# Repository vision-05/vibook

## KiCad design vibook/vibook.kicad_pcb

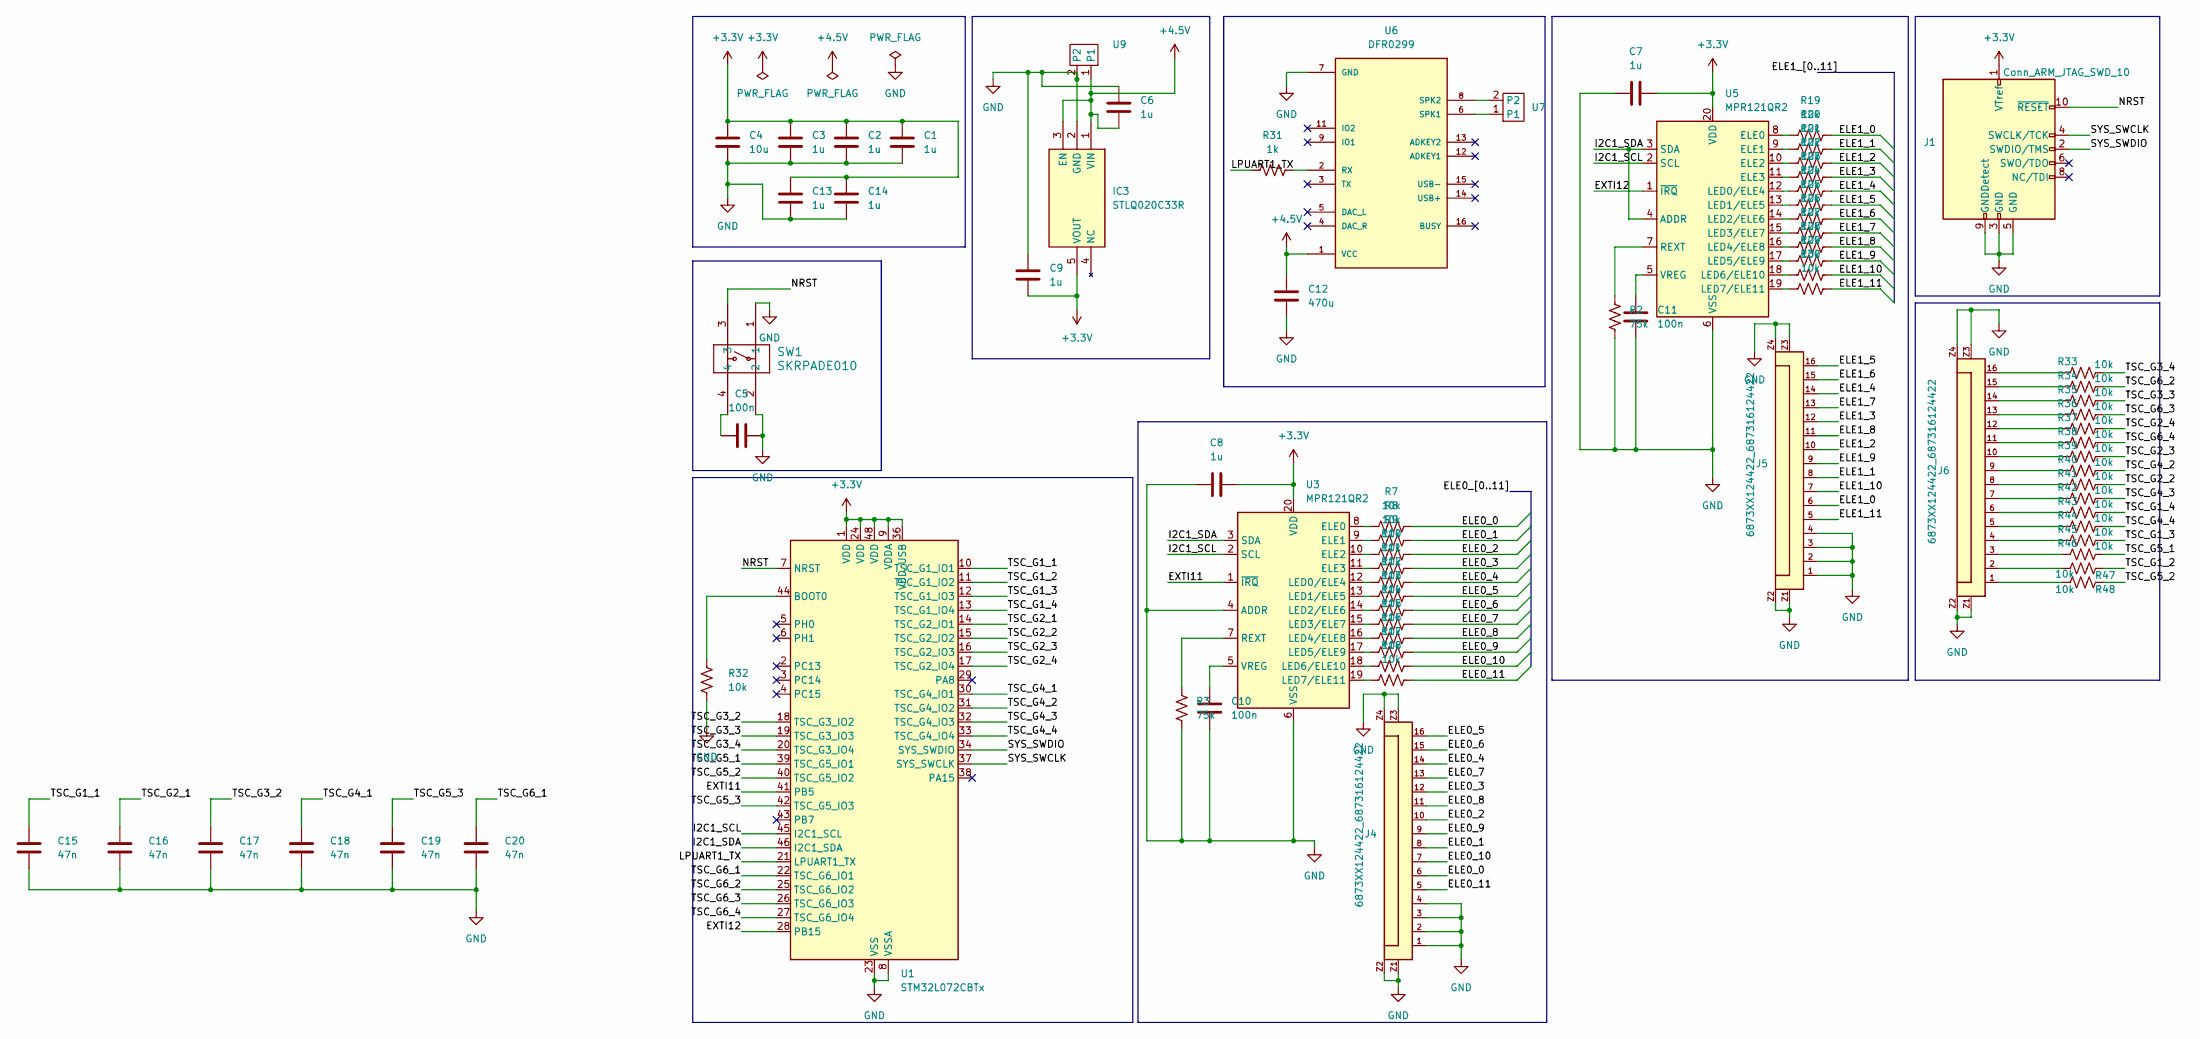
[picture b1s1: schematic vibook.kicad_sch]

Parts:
C1, C2, C3, C7, C8, C13, C14: 1u; C_0402_1005Metric
C4: 10u; C_0805_2012Metric
C5, C10, C11: 100n; C_0402_1005Metric
C6, C9: 1u; C_0805_2012Metric
C12: 470u; CP_EIA-7360-38_Kemet-E
C15, C16, C17, C18, C19, C20: 47n; C_0402_1005Metric
IC3: STLQ020C33R; SOT-353_SC-70-5; Manufacturer_Part_Number STLQ020C33R; Mouser Part Number 511-STLQ020C33R
J1: Conn_ARM_JTAG_SWD_10; PinHeader_2x05_P1.27mm_Vertical_SMD
J4, J5, J6: 6873XX124422_687316124422; 687316124422
R2, R3: 75k; R_0603_1608Metric
R7, R8, R9, R10, R11, R12, R13, R14, R15, R16, R17, R18, R19, R20, R21, R22, R23, R24, R25, R26, R27, R28, R29, R30, R32, R33, R34, R35, R36, R37, R38, R39, R40, R41, R42, R43, R44, R45, R46, R47, R48: 10k; R_0402_1005Metric
R31: 1k; R_0805_2012Metric
SW1: SKRPADE010; SKRPADE010_AAL
U1: STM32L072CBTx; LQFP-48_7x7mm_P0.5mm
U3, U5: MPR121QR2; UQFN-20_3x3mm_P0.4mm
U6: DFR0299; MODULE_DFR0299
U7, U9: Molex_PicoBlade_53047-0210_1x02_P1.25mm_Vertical

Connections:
+3.3V: C1.1, C2.1, C3.1, C4.1, C7.2, C8.2, C9.2, C13.1, C14.1, IC3.5 (VOUT), J1.1 (VTref), U1.1 (VDD), U1.9 (VDDA), U1.24 (VDD), U1.36 (VDD_USB), U1.48 (VDD), U3.20 (VDD), U5.20 (VDD)
+4.5V: C6.2, C12.2, IC3.1 (VIN), IC3.3 (EN), U6.1 (VCC), U9.1
/ELE0_0: J4.6, R7.2
/ELE0_1: J4.8, R8.2
/ELE0_2: J4.10, R9.2
/ELE0_3: J4.12, R10.2
/ELE0_4: J4.14, R11.2
/ELE0_5: J4.16, R12.2
/ELE0_6: J4.15, R13.2
/ELE0_7: J4.13, R14.2
/ELE0_8: J4.11, R15.2
/ELE0_9: J4.9, R16.2
/ELE0_10: J4.7, R17.2
/ELE0_11: J4.5, R18.2
/ELE1_0: J5.6, R19.2
/ELE1_1: J5.8, R20.2
/ELE1_2: J5.10, R21.2
/ELE1_3: J5.12, R22.2
/ELE1_4: J5.14, R23.2
/ELE1_5: J5.16, R24.2
/ELE1_6: J5.15, R25.2
/ELE1_7: J5.13, R26.2
/ELE1_8: J5.11, R27.2
/ELE1_9: J5.9, R28.2
/ELE1_10: J5.7, R29.2
/ELE1_11: J5.5, R30.2
/EXTI11: U1.41 (PB5), U3.1 (~IRQ)
/EXTI12: U1.28 (PB15), U5.1 (~IRQ)
/I2C1_SCL: U1.45 (I2C1_SCL), U3.2 (SCL), U5.2 (SCL)
/I2C1_SDA: U1.46 (I2C1_SDA), U3.3 (SDA), U5.3 (SDA), U5.4 (ADDR)
/LPUART1_TX: R31.1, U1.21 (LPUART1_TX)
/NRST: J1.10 (~RESET), SW1.3, U1.7 (NRST)
/SYS_SWCLK: J1.4 (SWCLK/TCK), U1.37 (SYS_SWCLK)
/SYS_SWDIO: J1.2 (SWDIO/TMS), U1.34 (SYS_SWDIO)
/TSC_G1_1: C15.1, U1.10 (TSC_G1_IO1)
/TSC_G1_2: R47.2, U1.11 (TSC_G1_IO2)
/TSC_G1_3: R45.2, U1.12 (TSC_G1_IO3)
/TSC_G1_4: R43.2, U1.13 (TSC_G1_IO4)
/TSC_G2_1: C16.1, U1.14 (TSC_G2_IO1)
/TSC_G2_2: R41.2, U1.15 (TSC_G2_IO2)
/TSC_G2_3: R39.2, U1.16 (TSC_G2_IO3)
/TSC_G2_4: R37.2, U1.17 (TSC_G2_IO4)
/TSC_G3_2: C17.1, U1.18 (TSC_G3_IO2)
/TSC_G3_3: R35.2, U1.19 (TSC_G3_IO3)
/TSC_G3_4: R33.2, U1.20 (TSC_G3_IO4)
/TSC_G4_1: C18.1, U1.30 (TSC_G4_IO1)
/TSC_G4_2: R40.2, U1.31 (TSC_G4_IO2)
/TSC_G4_3: R42.2, U1.32 (TSC_G4_IO3)
/TSC_G4_4: R44.2, U1.33 (TSC_G4_IO4)
/TSC_G5_1: R46.2, U1.39 (TSC_G5_IO1)
/TSC_G5_2: R48.2, U1.40 (TSC_G5_IO2)
/TSC_G5_3: C19.1, U1.42 (TSC_G5_IO3)
/TSC_G6_1: C20.1, U1.22 (TSC_G6_IO1)
/TSC_G6_2: R34.2, U1.25 (TSC_G6_IO2)
/TSC_G6_3: R36.2, U1.26 (TSC_G6_IO3)
/TSC_G6_4: R38.2, U1.27 (TSC_G6_IO4)
GND: C1.2, C2.2, C3.2, C4.2, C5.2, C6.1, C7.1, C8.1, C9.1, C10.2, C11.2, C12.1, C13.2, C14.2, C15.2, C16.2, C17.2, C18.2, C19.2, C20.2, IC3.2 (GND), J1.3 (GND), J1.5 (GND), J1.9 (GNDDetect), J4.1, J4.2, J4.3, J4.4, J4.Z1, J4.Z2, J4.Z3, J4.Z4, J5.1, J5.2, J5.3, J5.4, J5.Z1, J5.Z2, J5.Z3, J5.Z4, J6.Z1, J6.Z2, J6.Z3, J6.Z4, R2.1, R3.1, R32.2, SW1.1, SW1.2, U1.8 (VSSA), U1.23 (VSS), U1.35 (VSS), U1.47 (VSS), U3.4 (ADDR), U3.6 (VSS), U5.6 (VSS), U6.7 (GND), U6.10 (GND), U9.2
unnamed: C5.1, SW1.4
unnamed: J6.1, R48.1
unnamed: J6.2, R47.1
unnamed: J6.3, R46.1
unnamed: J6.4, R45.1
unnamed: J6.5, R44.1
unnamed: J6.6, R43.1
unnamed: J6.7, R42.1
unnamed: J6.8, R41.1
unnamed: J6.9, R40.1
unnamed: J6.10, R39.1
unnamed: J6.11, R38.1
unnamed: J6.12, R37.1
unnamed: J6.13, R36.1
unnamed: J6.14, R35.1
unnamed: J6.15, R34.1
unnamed: J6.16, R33.1
unnamed: R32.1, U1.44 (BOOT0)
unnamed: R7.1, U3.8 (ELE0)
unnamed: R8.1, U3.9 (ELE1)
unnamed: R9.1, U3.10 (ELE2)
unnamed: R10.1, U3.11 (ELE3)
unnamed: R11.1, U3.12 (LED0/ELE4)
unnamed: R12.1, U3.13 (LED1/ELE5)
unnamed: R13.1, U3.14 (LED2/ELE6)
unnamed: R14.1, U3.15 (LED3/ELE7)
unnamed: R15.1, U3.16 (LED4/ELE8)
unnamed: R16.1, U3.17 (LED5/ELE9)
unnamed: R17.1, U3.18 (LED6/ELE10)
unnamed: R18.1, U3.19 (LED7/ELE11)
unnamed: R3.2, U3.7 (REXT)
unnamed: C10.1, U3.5 (VREG)
unnamed: R19.1, U5.8 (ELE0)
unnamed: R20.1, U5.9 (ELE1)
unnamed: R21.1, U5.10 (ELE2)
unnamed: R22.1, U5.11 (ELE3)
unnamed: R23.1, U5.12 (LED0/ELE4)
unnamed: R24.1, U5.13 (LED1/ELE5)
unnamed: R25.1, U5.14 (LED2/ELE6)
unnamed: R26.1, U5.15 (LED3/ELE7)
unnamed: R27.1, U5.16 (LED4/ELE8)
unnamed: R28.1, U5.17 (LED5/ELE9)
unnamed: R29.1, U5.18 (LED6/ELE10)
unnamed: R30.1, U5.19 (LED7/ELE11)
unnamed: R2.2, U5.7 (REXT)
unnamed: C11.1, U5.5 (VREG)
unnamed: R31.2, U6.2 (RX)
unnamed: U6.6 (SPK1), U7.1
unnamed: U6.8 (SPK2), U7.2

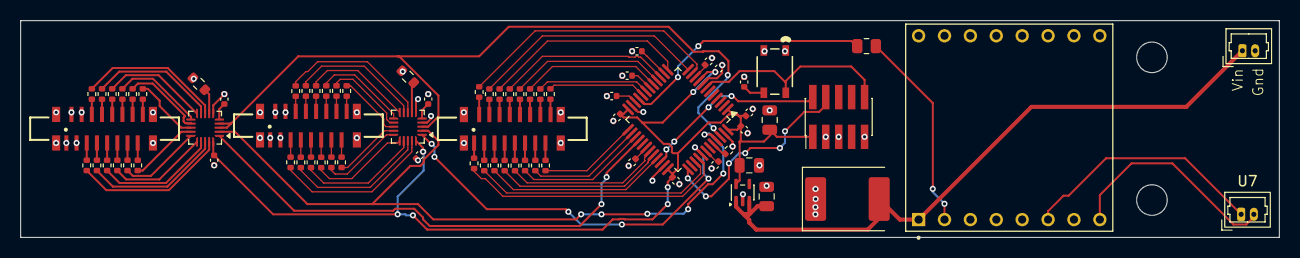
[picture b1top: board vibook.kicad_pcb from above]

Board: 2 copper layers, 123.5 x 21.3 mm, 76 parts (0 on the bottom side), 106 nets.

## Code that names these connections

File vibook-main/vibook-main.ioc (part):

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Mcu.Name=STM32L072C(B-Z)Tx
Mcu.Package=LQFP48
Mcu.UserName=STM32L072CBTx
PA0.Mode=G1_IO1-Sampling
PA0.Signal=TSC_G1_IO1
PA1.Mode=G1_IO2-Channel
PA1.Signal=TSC_G1_IO2
PA10.Mode=G4_IO2-Channel
PA10.Signal=TSC_G4_IO2
PA11.Mode=G4_IO3-Channel
PA11.Signal=TSC_G4_IO3
PA12.Mode=G4_IO4-Channel
PA12.Signal=TSC_G4_IO4
PA13.Mode=Serial_Wire
PA13.Signal=SYS_SWDIO
PA14.Mode=Serial_Wire
PA14.Signal=SYS_SWCLK
PA2.Mode=G1_IO3-Channel
PA2.Signal=TSC_G1_IO3
PA3.Mode=G1_IO4-Channel
PA3.Signal=TSC_G1_IO4
PA4.Mode=G2_IO1-Sampling
PA4.Signal=TSC_G2_IO1
PA5.Mode=G2_IO2-Channel
PA5.Signal=TSC_G2_IO2
PA6.Mode=G2_IO3-Channel
PA6.Signal=TSC_G2_IO3
PA7.Mode=G2_IO4-Channel
PA7.Signal=TSC_G2_IO4
PA9.Mode=G4_IO1-Sampling
PA9.Signal=TSC_G4_IO1
PB0.Mode=G3_IO2-Sampling
PB0.Signal=TSC_G3_IO2
PB1.Mode=G3_IO3-Channel
PB1.Signal=TSC_G3_IO3
PB10.Mode=Half_duplex(single_wire_mode)
PB10.Signal=LPUART1_TX
PB11.Mode=G6_IO1-Sampling
PB11.Signal=TSC_G6_IO1
PB12.Mode=G6_IO2-Channel
PB12.Signal=TSC_G6_IO2
PB13.Mode=G6_IO3-Channel
PB13.Signal=TSC_G6_IO3
PB14.Mode=G6_IO4-Channel
PB14.Signal=TSC_G6_IO4
PB15.GPIOParameters=GPIO_ModeDefaultEXTI
PB15.GPIO_ModeDefaultEXTI=GPIO_MODE_IT_FALLING
PB15.Signal=GPXTI15
PB2.Mode=G3_IO4-Channel
PB2.Signal=TSC_G3_IO4
PB3.Mode=G5_IO1-Channel
PB3.Signal=TSC_G5_IO1
PB4.Mode=G5_IO2-Channel
PB4.Signal=TSC_G5_IO2
PB5.GPIOParameters=GPIO_ModeDefaultEXTI
PB5.GPIO_ModeDefaultEXTI=GPIO_MODE_IT_FALLING
PB5.Signal=GPXTI5
PB6.Mode=G5_IO3-Sampling
PB6.Signal=TSC_G5_IO3
PB7.Mode=G5_IO4-Channel
PB7.Signal=TSC_G5_IO4
PB8.Mode=I2C
PB8.Signal=I2C1_SCL
PB9.Mode=I2C
PB9.Signal=I2C1_SDA
RCC.HSE_VALUE=8000000
RCC.SYSCLKFreq_VALUE=2097000
board=custom

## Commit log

2026-03-25 complete design
2026-03-25 added kicad files
2026-03-31 Got multiplexing working
2026-04-02 updated board design
2026-04-06 updated schematic
2026-04-07 changed ffc connectors and added different mcu
2026-04-10 started mcu upgrade and rerouting
2026-05-07 finished spine pcb final design, sent for manufacture
2026-05-14 started code
2026-05-14 merging
